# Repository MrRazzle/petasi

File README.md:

# Razzle designs a keyboard
Attempt number 1 at creating a keyboard

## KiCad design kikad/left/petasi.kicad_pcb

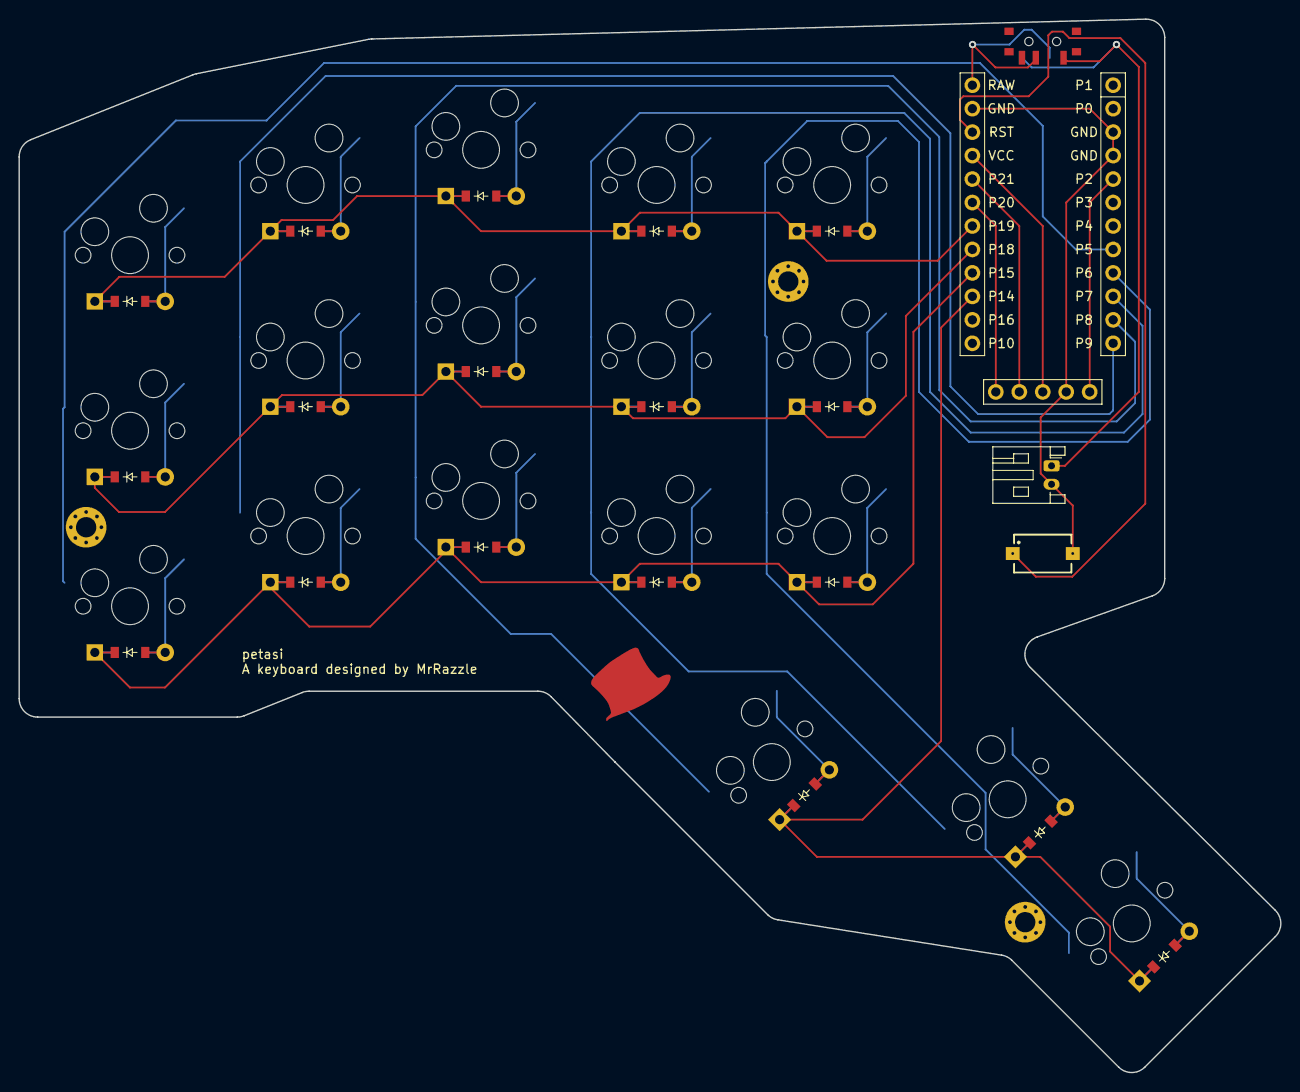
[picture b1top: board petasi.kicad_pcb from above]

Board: 2 copper layers, 136.6 x 114.0 mm, 44 parts (0 on the bottom side), 35 nets.

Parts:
D1, D2, D3, D4, D5, D6, D7, D8, D9, D10, D11, D12, D13, D14, D15, D16, D17, D18: ComboDiode
DISP1: display_nice_view
MCU1: mcu_nice_nano
S1, S2, S3, S4, S5, S6, S7, S8, S9, S10, S11, S12, S13, S14, S15, S16, S17, S18: MX
S19: 434121025816
T1: SW_SPDT_PCM12
_1: JST_PH_S2B-PH-K_1x02_P2.00mm_Horizontal
_4, _5, _6: MountingHole_2.2mm_M2_Pad_Via

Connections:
GND: DISP1.4, MCU1.3, MCU1.4, MCU1.23, S19.2, _1.2
P2: DISP1.5, MCU1.5
P5: MCU1.8, S1.1, S2.1, S3.1
P6: MCU1.9, S13.1, S14.1, S15.1, S17.1
P7: MCU1.10, S10.1, S11.1, S12.1, S16.1
P8: MCU1.11, S7.1, S8.1, S9.1, S18.1
P9: MCU1.12, S4.1, S5.1, S6.1
P14: D16.1, D17.1, D18.1, MCU1.15
P15: D1.1, D4.1, D7.1, D10.1, D13.1, MCU1.16
P18: D2.1, D5.1, D8.1, D11.1, D14.1, MCU1.17
P19: D3.1, D6.1, D9.1, D12.1, D15.1, MCU1.18
P20: DISP1.1, MCU1.19
P21: DISP1.2, MCU1.20
RAW: MCU1.24, T1.2
RST: MCU1.22, S19.1
VCC: DISP1.3, MCU1.21
index2_bot: D13.2, S13.2
index2_mid: D14.2, S14.2
index2_top: D15.2, S15.2
index_bot: D10.2, S10.2
index_mid: D11.2, S11.2
index_top: D12.2, S12.2
middle_bot: D7.2, S7.2
middle_mid: D8.2, S8.2
middle_top: D9.2, S9.2
one_single: D16.2, S16.2
pinkie_bot: D1.2, S1.2
pinkie_mid: D2.2, S2.2
pinkie_top: D3.2, S3.2
pos: T1.1, _1.1
ring_bot: D4.2, S4.2
ring_mid: D5.2, S5.2
ring_top: D6.2, S6.2
three_single: D18.2, S18.2
two_single: D17.2, S17.2

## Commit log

2024-10-06 Update LICENSE
2024-10-07 Add 3D case
2024-10-07 3D printed case
2024-10-07 Left-final-gen
2024-10-07 Fix-left-wall
2024-10-08 More changes
2024-10-12 Add screen and move power switch
2024-10-12 Finish Row Net
2024-10-12 Finished Left Side
2024-10-13 Start ZMK
2024-10-13 Initial ZMK
2024-10-13 ZMK initial
2024-10-13 change extention
2024-10-13 Keymap
2024-10-13 Change zmk folder
